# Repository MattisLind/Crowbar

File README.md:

# Crowbar

A design for a simple crowbar based on circuit I found on a [webpage](http://axotron.se/index_en.php?page=26).

The project is also avilable at oshpark as a shared [project](https://oshpark.com/shared_projects/hjerPtfs).

All gerbers are avilable here as well as the diptrace file.

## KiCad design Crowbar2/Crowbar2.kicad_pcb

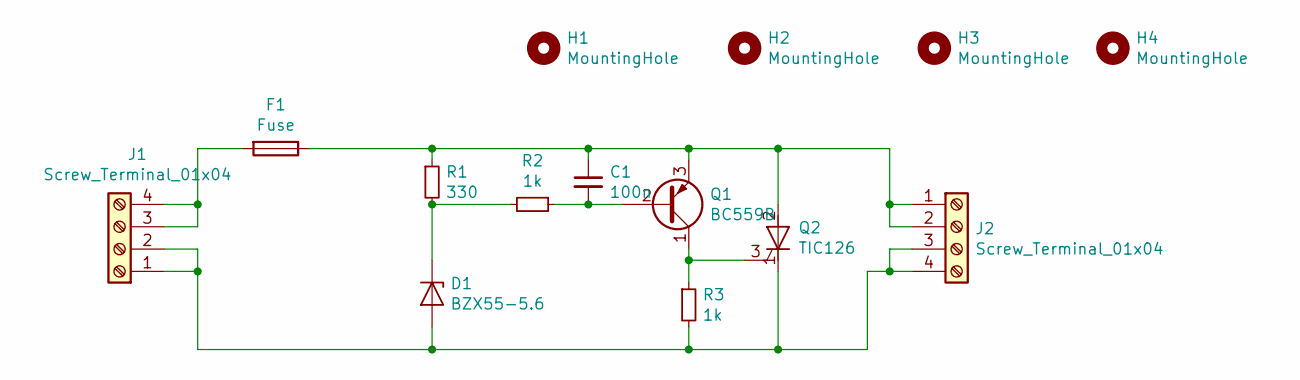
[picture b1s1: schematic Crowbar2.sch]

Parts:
C1: 100n; C_Disc_D5.0mm_W2.5mm_P5.00mm
D1: BZX55-5.6; D_DO-35_SOD27_P7.62mm_Horizontal
F1: Fuse; Fuse holder
H1, H2, H3, H4: MountingHole; MountingHole_3.2mm_M3
J1, J2: Screw_Terminal_01x04; TerminalBlock_Phoenix_MKDS-1,5-4_1x04_P5.00mm_Horizontal
Q1: BC559B; TO-92
Q2: TIC126; TO-220-3_Vertical
R1: 330; R_Axial_DIN0207_L6.3mm_D2.5mm_P10.16mm_Horizontal
R2, R3: 1k; R_Axial_DIN0207_L6.3mm_D2.5mm_P10.16mm_Horizontal

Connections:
unnamed: C1.1, F1.1, J2.1, J2.2, Q1.3 (E), Q2.2 (A), R1.1
unnamed: C1.2, Q1.2 (B), R2.1
unnamed: D1.1 (K), R1.2, R2.2
unnamed: D1.2 (A), J1.1, J1.2, J2.3, J2.4, Q2.1 (K), R3.2
unnamed: F1.2, J1.3, J1.4
unnamed: Q1.1 (C), Q2.3 (G), R3.1

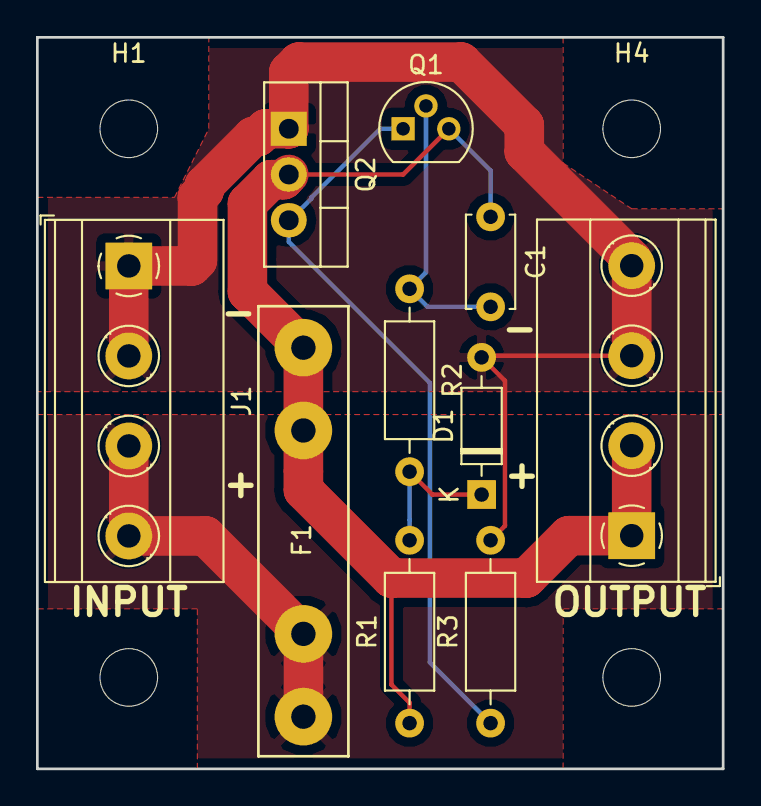
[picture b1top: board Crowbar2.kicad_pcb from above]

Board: 2 copper layers, 38.1 x 40.6 mm, 14 parts (0 on the bottom side), 6 nets.

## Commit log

2016-11-20 First commit of Crowbar
2016-11-20 First issue
2022-01-22 Made a new crowbar but with a simple zener and transistor this time. Included a fuse holder and mountingholes.
